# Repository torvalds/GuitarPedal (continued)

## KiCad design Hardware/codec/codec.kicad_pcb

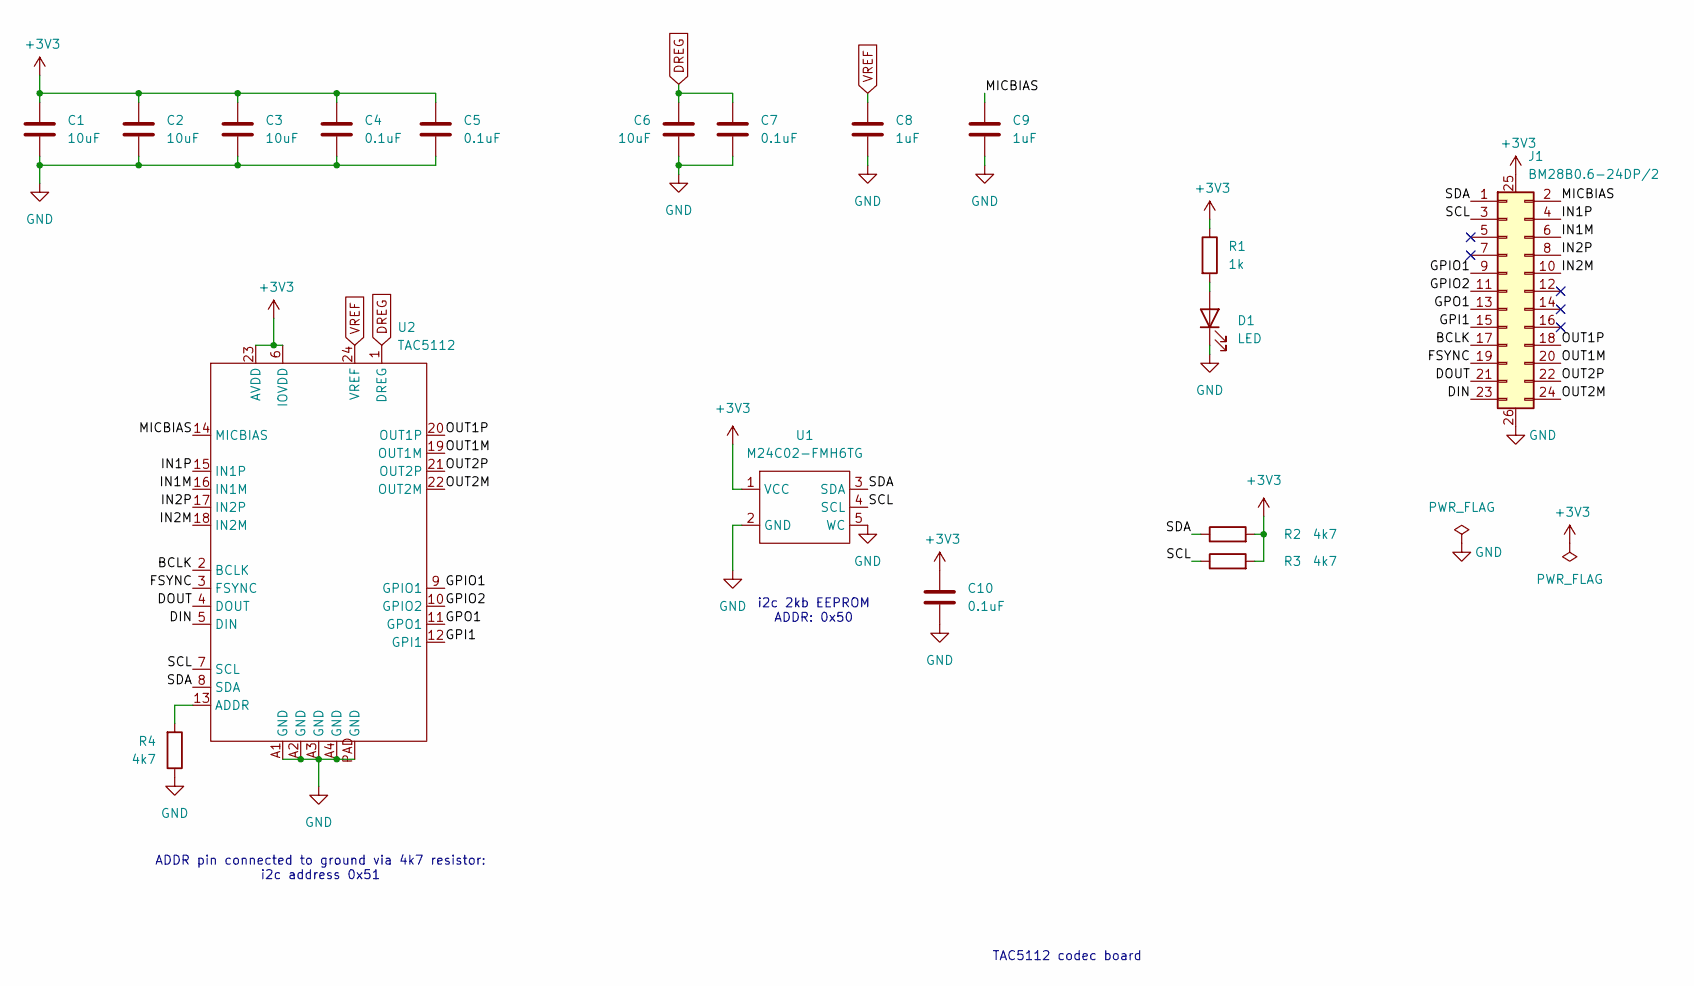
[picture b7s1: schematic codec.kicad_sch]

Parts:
C1, C2, C3, C6: 10uF; C_0603_1608Metric; LCSC PN C91606
C4, C5, C7, C10: 0.1uF; C_0402_1005Metric; LCSC PN C1525
C8, C9: 1uF; C_0603_1608Metric; LCSC PN C519560
D1: LED; LED_0402_1005Metric; LCSC PN C160479
J1: BM28B0.6-24DP/2; BM28B0.6-24DP; LCSC PN C424568
R1: 1k; R_0402_1005Metric; LCSC PN C11702
R2, R3, R4: 4k7; R_0402_1005Metric; JLCPCB C25900
U1: M24C02-FMH6TG; UFDFPN5; JLCPCB C222197
U2: TAC5112; LCSC PN C44853692

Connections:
+3V3: C1.1, C2.1, C3.1, C4.1, C5.1, C10.1, J1.25 (PWR1), R1.1, R2.2, R3.2, U1.1 (VCC), U2.6 (IOVDD), U2.23 (AVDD)
/BCLK: J1.17, U2.2 (BCLK)
/DIN: J1.23, U2.5 (DIN)
/DOUT: J1.21, U2.4 (DOUT)
/FSYNC: J1.19, U2.3 (FSYNC)
/GPI1: J1.15, U2.12 (GPI1)
/GPIO1: J1.9, U2.9 (GPIO1)
/GPIO2: J1.11, U2.10 (GPIO2)
/GPO1: J1.13, U2.11 (GPO1)
/IN1M: J1.6, U2.16 (IN1M)
/IN1P: J1.4, U2.15 (IN1P)
/IN2M: J1.10, U2.18 (IN2M)
/IN2P: J1.8, U2.17 (IN2P)
/MICBIAS: C9.1, J1.2, U2.14 (MICBIAS)
/OUT1M: J1.20, U2.19 (OUT1M)
/OUT1P: J1.18, U2.20 (OUT1P)
/OUT2M: J1.24, U2.22 (OUT2M)
/OUT2P: J1.22, U2.21 (OUT2P)
/SCL: J1.3, R3.1, U1.4 (SCL), U2.7 (SCL)
/SDA: J1.1, R2.1, U1.3 (SDA), U2.8 (SDA)
DREG: C6.1, C7.1, U2.1 (DREG)
GND: C1.2, C2.2, C3.2, C4.2, C5.2, C6.2, C7.2, C8.2, C9.2, C10.2, D1.1 (K), J1.26 (PWR1), R4.1, U1.2 (GND), U1.5 (WC), U2.A1 (GND), U2.A2 (GND), U2.A3 (GND), U2.A4 (GND), U2.PAD (GND)
unnamed: D1.2 (A), R1.2
unnamed: R4.2, U2.13 (ADDR)
VREF: C8.1, U2.24 (VREF)

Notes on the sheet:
TAC5112 codec board
ADDR pin connected to ground via 4k7 resistor: i2c address 0x51
i2c 2kb EEPROM ADDR: 0x50

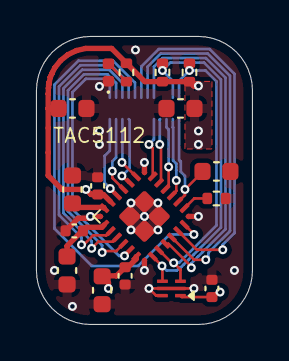
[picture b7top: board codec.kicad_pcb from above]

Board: 4 copper layers, 12.0 x 16.0 mm, 18 parts (1 on the bottom side), 25 nets.

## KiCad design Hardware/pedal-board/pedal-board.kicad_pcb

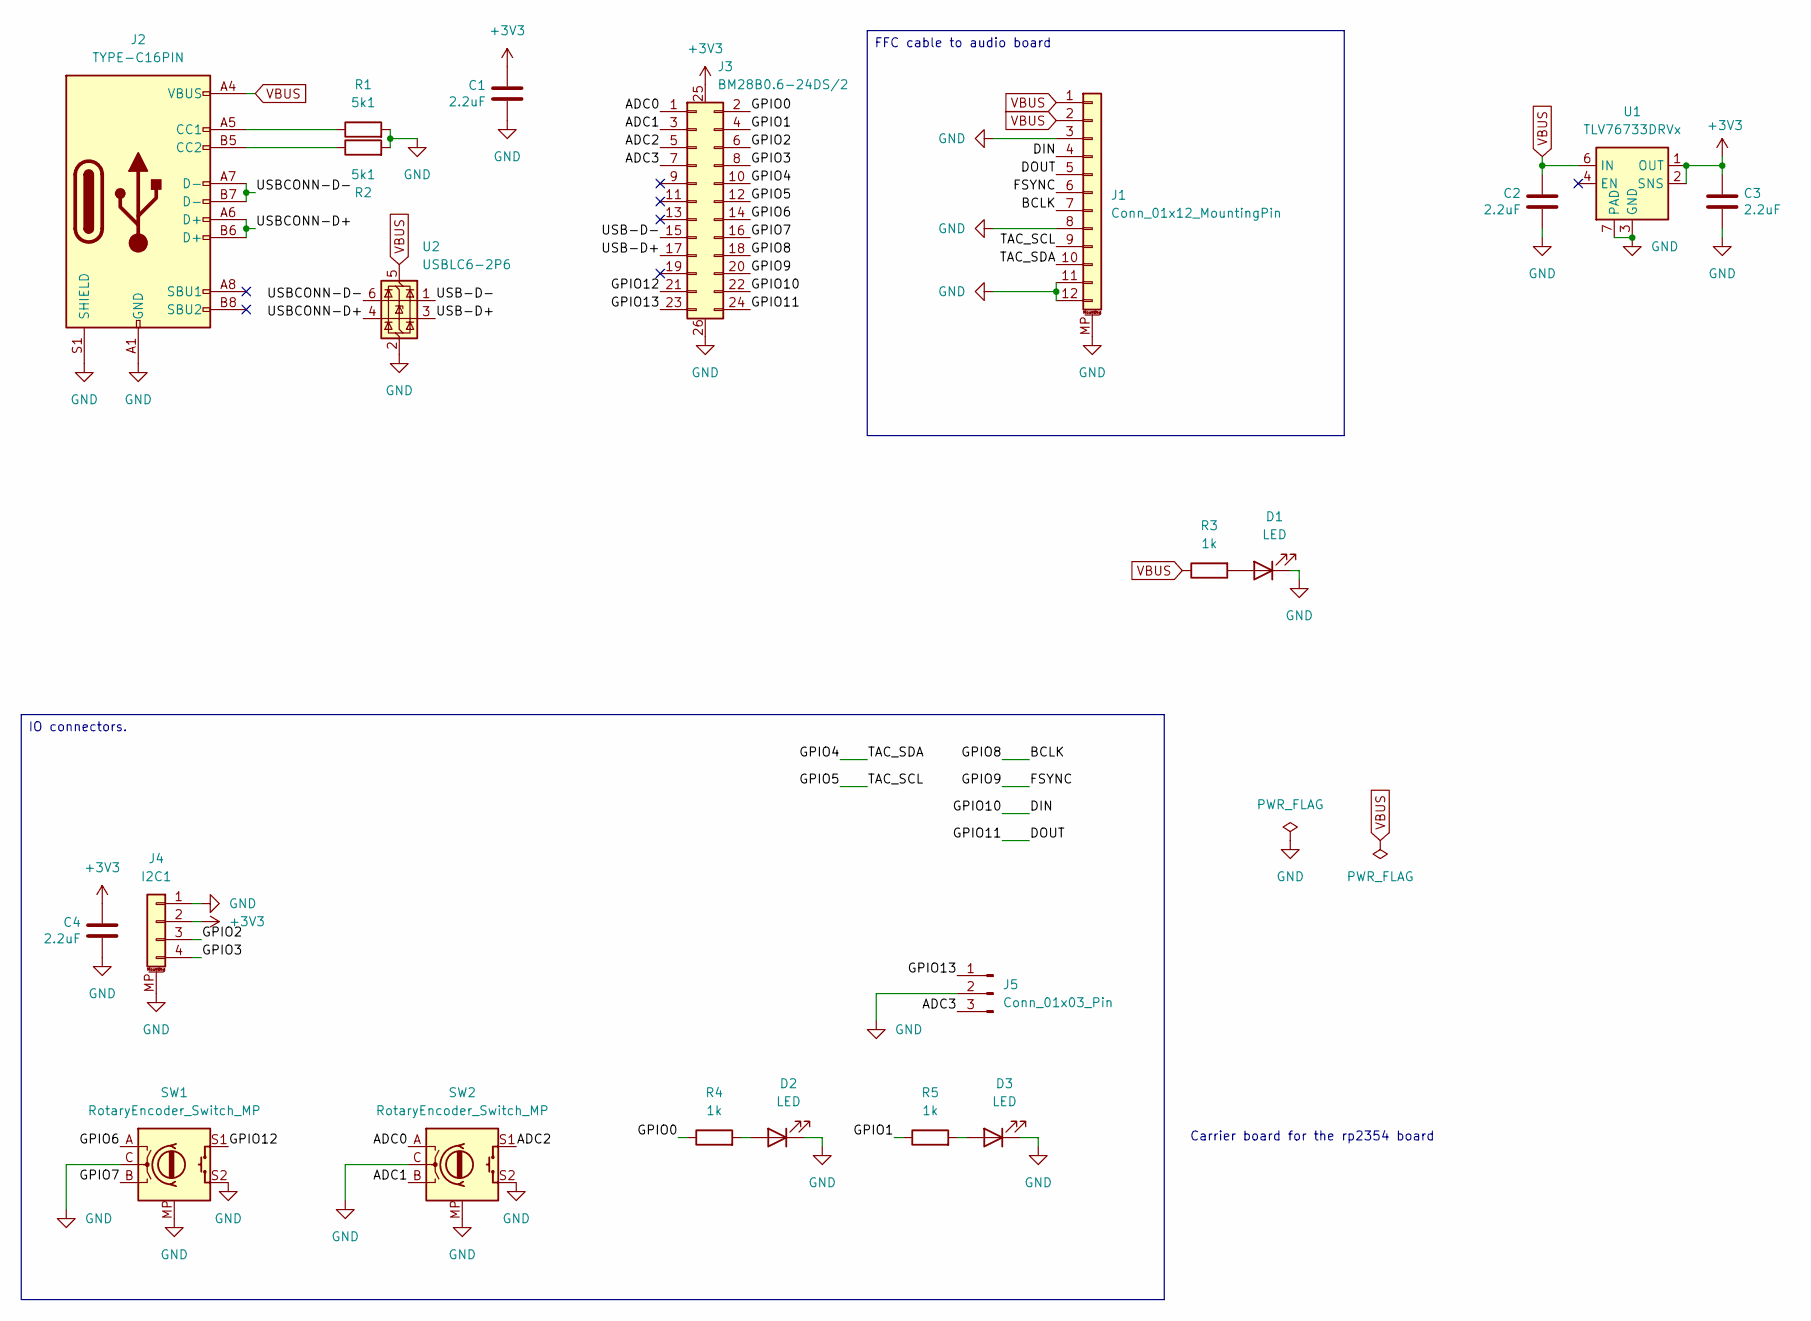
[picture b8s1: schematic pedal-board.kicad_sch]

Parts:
C1, C2, C3, C4: 2.2uF; C_0805_2012Metric; LCSC PN C77081
D1: LED; LED_0402_1005Metric; LCSC PN C160479
D2, D3: LED; LED_D5.0mm_FlatTop
J1: Conn_01x12_MountingPin; AFH-5-S12FIA-1H; LCSC PN C5371161
J2: TYPE-C16PIN; USB_C_Receptacle_G-Switch_GT-USB-7051x; LCSC PN C2843970
J3: BM28B0.6-24DS/2; BM28B0.6-24DS; LCSC PN C424569
J4: I2C1; JST_SH_SM04B-SRSS-TB_1x04-1MP_P1.00mm_Horizontal; JLCPCB C160404
J5: Conn_01x03_Pin; PinHeader_1x03_P2.54mm_Vertical
R1, R2: 5k1; R_0402_1005Metric; LCSC PN C25905
R3, R4, R5: 1k; R_0402_1005Metric; LCSC PN C11702
SW1, SW2: RotaryEncoder_Switch_MP; RotaryEncoder_Alps_EC11E-Switch_Vertical_H20mm
U1: TLV76733DRVx; WSON-6-1EP_2x2mm_P0.65mm_EP1x1.6mm; LCSC PN C2848334
U2: USBLC6-2P6; SOT-666; LCSC PN C15999

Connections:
+3V3: C1.1, C3.1, C4.1, J3.25 (PWR1), J4.2, U1.1 (OUT), U1.2 (SNS)
/ADC0: J3.1, SW2.A
/ADC1: J3.3, SW2.B
/ADC2: J3.5, SW2.S1
/ADC3: J3.7, J5.3
/BCLK: J1.7, J3.18
/DIN: J1.4, J3.22
/DOUT: J1.5, J3.24
/FSYNC: J1.6, J3.20
/GPIO0: J3.2, R4.1
/GPIO1: J3.4, R5.1
/GPIO2: J3.6, J4.3
/GPIO3: J3.8, J4.4
/GPIO4: J1.10, J3.10
/GPIO5: J1.9, J3.12
/GPIO6: J3.14, SW1.A
/GPIO7: J3.16, SW1.B
/GPIO12: J3.21, SW1.S1
/GPIO13: J3.23, J5.1
/USB-D+: J3.17, U2.3 (I/O2)
/USB-D-: J3.15, U2.1 (I/O1)
/USBCONN-D+: J2.A6 (D+), J2.B6 (D+), U2.4 (I/O2)
/USBCONN-D-: J2.A7 (D-), J2.B7 (D-), U2.6 (I/O1)
GND: C1.2, C2.2, C3.2, C4.2, D1.1 (K), D2.1 (K), D3.1 (K), J1.3, J1.8, J1.11, J1.12, J1.MP (MountPin), J2.A1 (GND), J2.A12 (GND), J2.B1 (GND), J2.B12 (GND), J2.S1 (SHIELD), J3.26 (PWR1), J4.1, J4.MP (MountPin), J5.2, R1.2, R2.2, SW1.C, SW1.MP, SW1.S2, SW2.C, SW2.MP, SW2.S2, U1.3 (GND), U1.5 (GND), U1.7 (PAD), U2.2 (GND)
unnamed: D1.2 (A), R3.2
unnamed: D2.2 (A), R4.2
unnamed: D3.2 (A), R5.2
unnamed: J2.A5 (CC1), R1.1
unnamed: J2.B5 (CC2), R2.1
VBUS: C2.1, J1.1, J1.2, J2.A4 (VBUS), J2.A9 (VBUS), J2.B4 (VBUS), J2.B9 (VBUS), R3.1, U1.6 (IN), U2.5 (VBUS)

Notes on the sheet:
Carrier board for the rp2354 board
IO connectors.
FFC cable to audio board

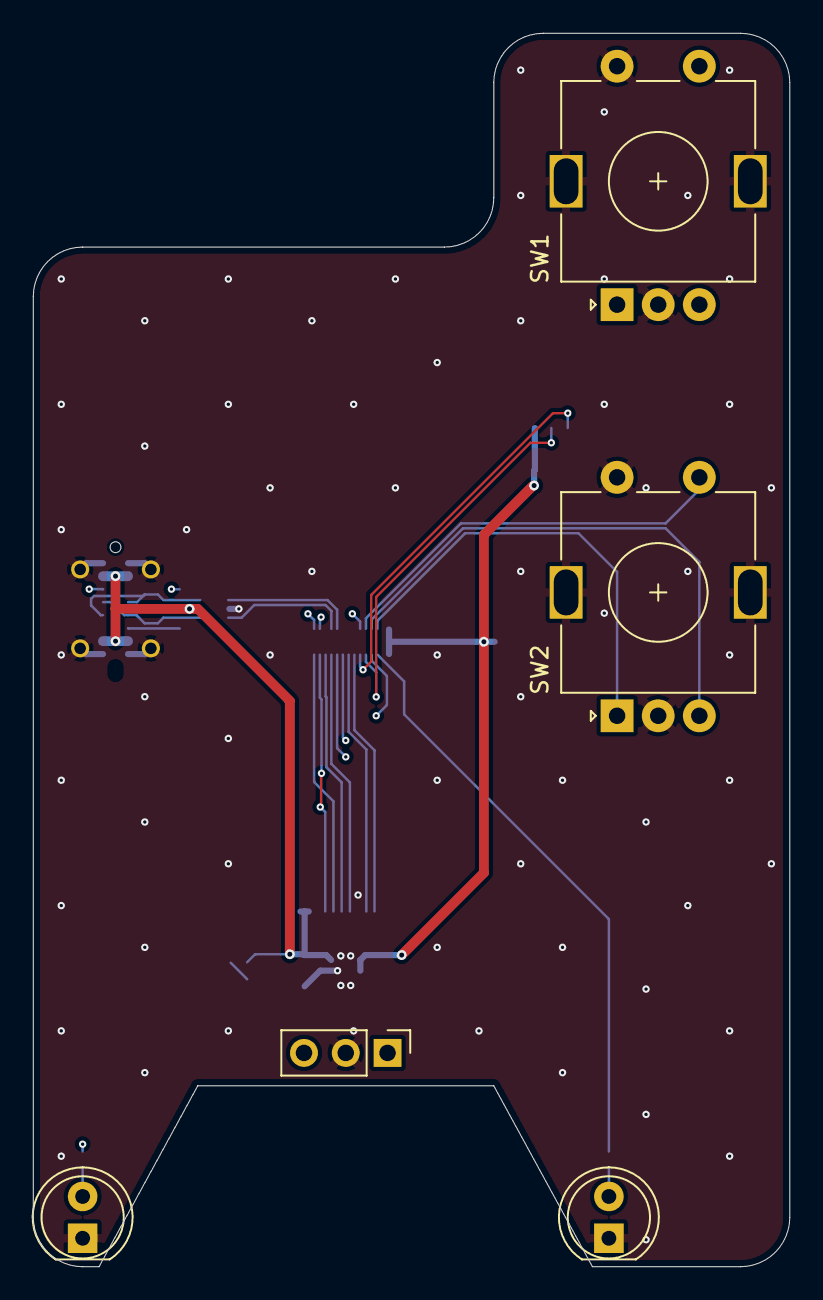
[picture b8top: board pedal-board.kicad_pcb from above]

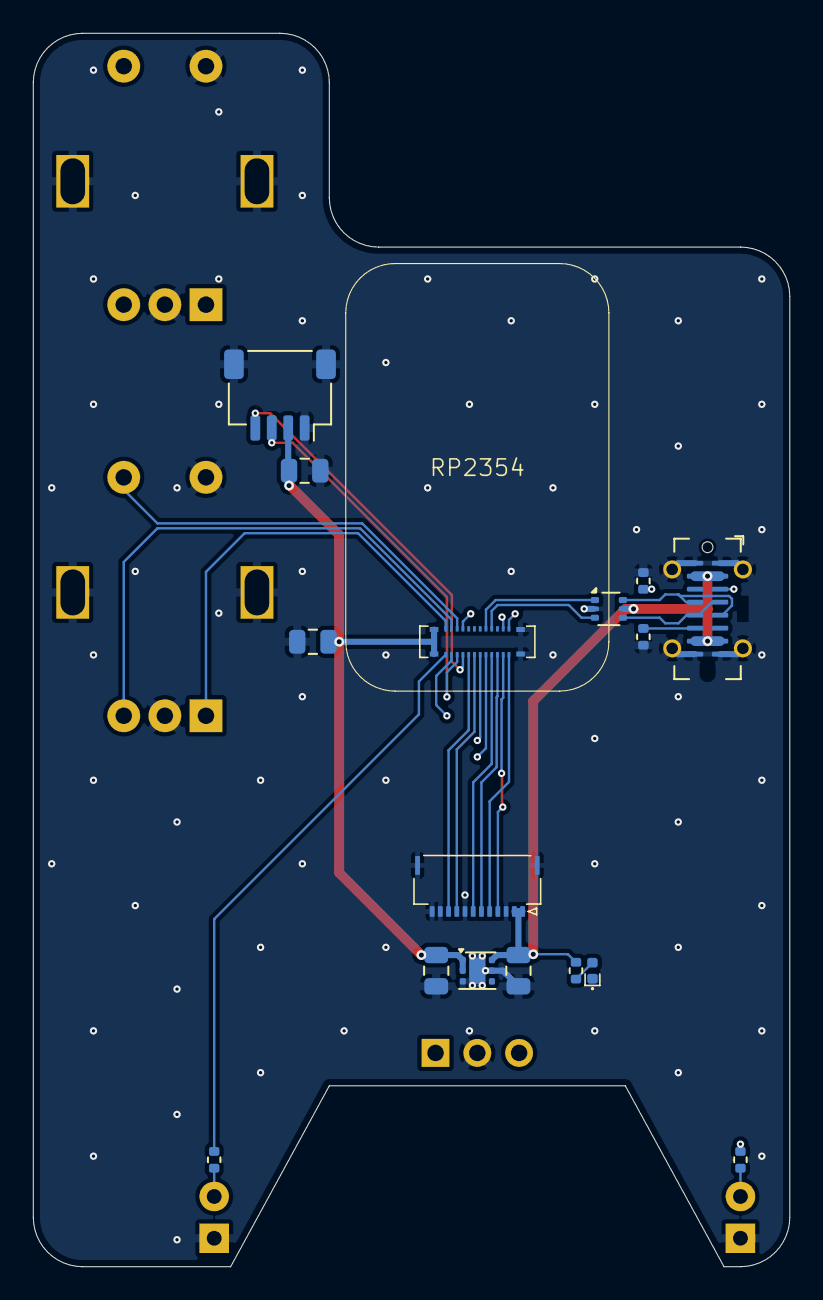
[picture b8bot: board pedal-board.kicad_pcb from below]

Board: 4 copper layers, 46.0 x 75.0 mm, 21 parts (16 on the bottom side), 30 nets.
